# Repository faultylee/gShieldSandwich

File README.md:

gShieldSandwich
===============

A sandwich board between UNO and gShield to provide fan cooling and connection breakout for additional Gbrl I/O

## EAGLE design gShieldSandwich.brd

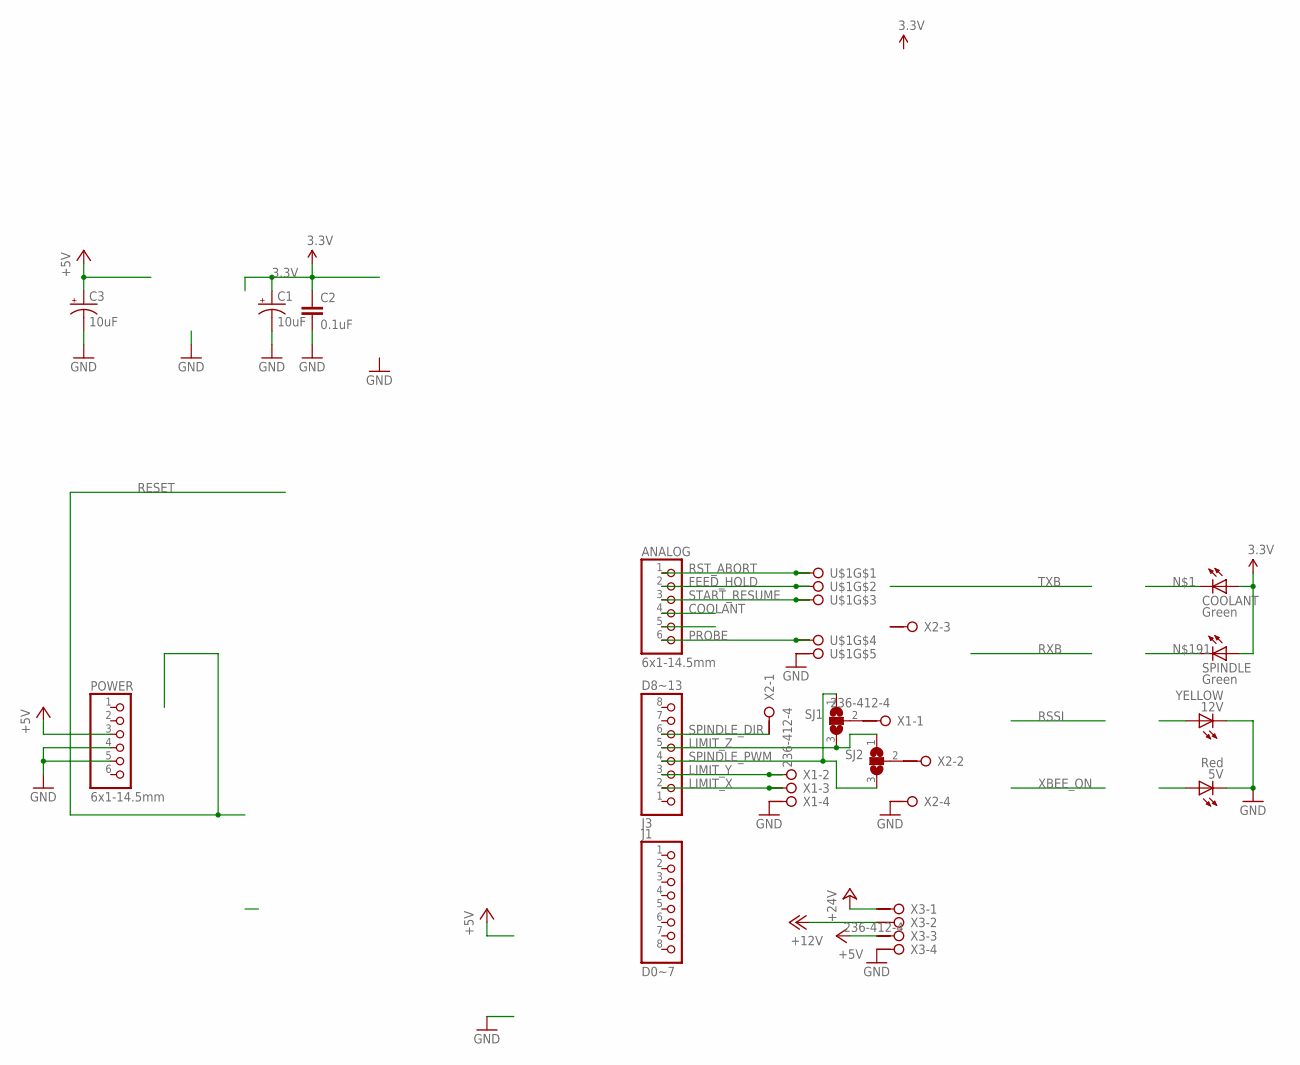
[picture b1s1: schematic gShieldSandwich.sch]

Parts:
5V: Red; CHIP-LED0805
12V: YELLOW; CHIP-LED0805
ANALOG: 6x1-14.5mm; 1X06
C1, C3: 10uF; EIA3216
C2: 0.1uF; 0603-CAP
COOLANT: Green; CHIP-LED0805
J1: D0~7; 1X08
J3: D8~13; 1X08
POWER: 6x1-14.5mm; 1X06
SJ1, SJ2: SJ2WW; SJ_2W
SPINDLE: Green; CHIP-LED0805
U$1: 236-412-5
X1, X2, X3: 236-412-4

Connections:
3.3V: C1.A (+), C2.1, COOLANT.A, SPINDLE.A
+5V: C3.A (+), POWER.3, X3.3@1 (KL1)
+12V: X3.2@1 (KL1)
+24V: X3.1@1 (KL1)
COOLANT: ANALOG.4
FEED_HOLD: ANALOG.2, U$1.2@1 (KL1), U$1.2@2 (KL2)
GND: 5V.C, 12V.C, C1.C (-), C2.2, C3.C (-), POWER.4, POWER.5, X3.4@1 (KL1)
LIMIT_X: J3.2, X1.3@1 (KL1), X1.3@2 (KL2)
LIMIT_Y: J3.3, X1.2@1 (KL1), X1.2@2 (KL2)
LIMIT_Z: J3.5, SJ1.3, SJ2.1
unnamed: SJ1.2, X1.1@1 (KL1)
unnamed: SJ2.2, X2.2@1 (KL1)
PROBE: ANALOG.6, U$1.4@1 (KL1), U$1.4@2 (KL2)
RST_ABORT: ANALOG.1, U$1.1@1 (KL1), U$1.1@2 (KL2)
SPINDLE_DIR: J3.6, X2.1@1 (KL1)
SPINDLE_PWM: J3.4, SJ1.1, SJ2.3
START_RESUME: ANALOG.3, U$1.3@1 (KL1), U$1.3@2 (KL2)

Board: 2 copper layers, 17 parts (0 on the bottom side), 14 nets, no tracks yet.
